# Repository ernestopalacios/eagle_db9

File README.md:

# eagle_db9

ESPAÑOL:    

Esta librería esta destinada al diseño de tarjetas electronicas que permitan, adaptar los diferentes tipos de conectores seriales. Muchas veces necesitamos conectar dos elementos y es necesario adaptar el tipo de conector. 

Mediante el uso de estas tarjetas diseñadas en Eagle PCB se lo puede lograr de una manera mucho mas sencilla.

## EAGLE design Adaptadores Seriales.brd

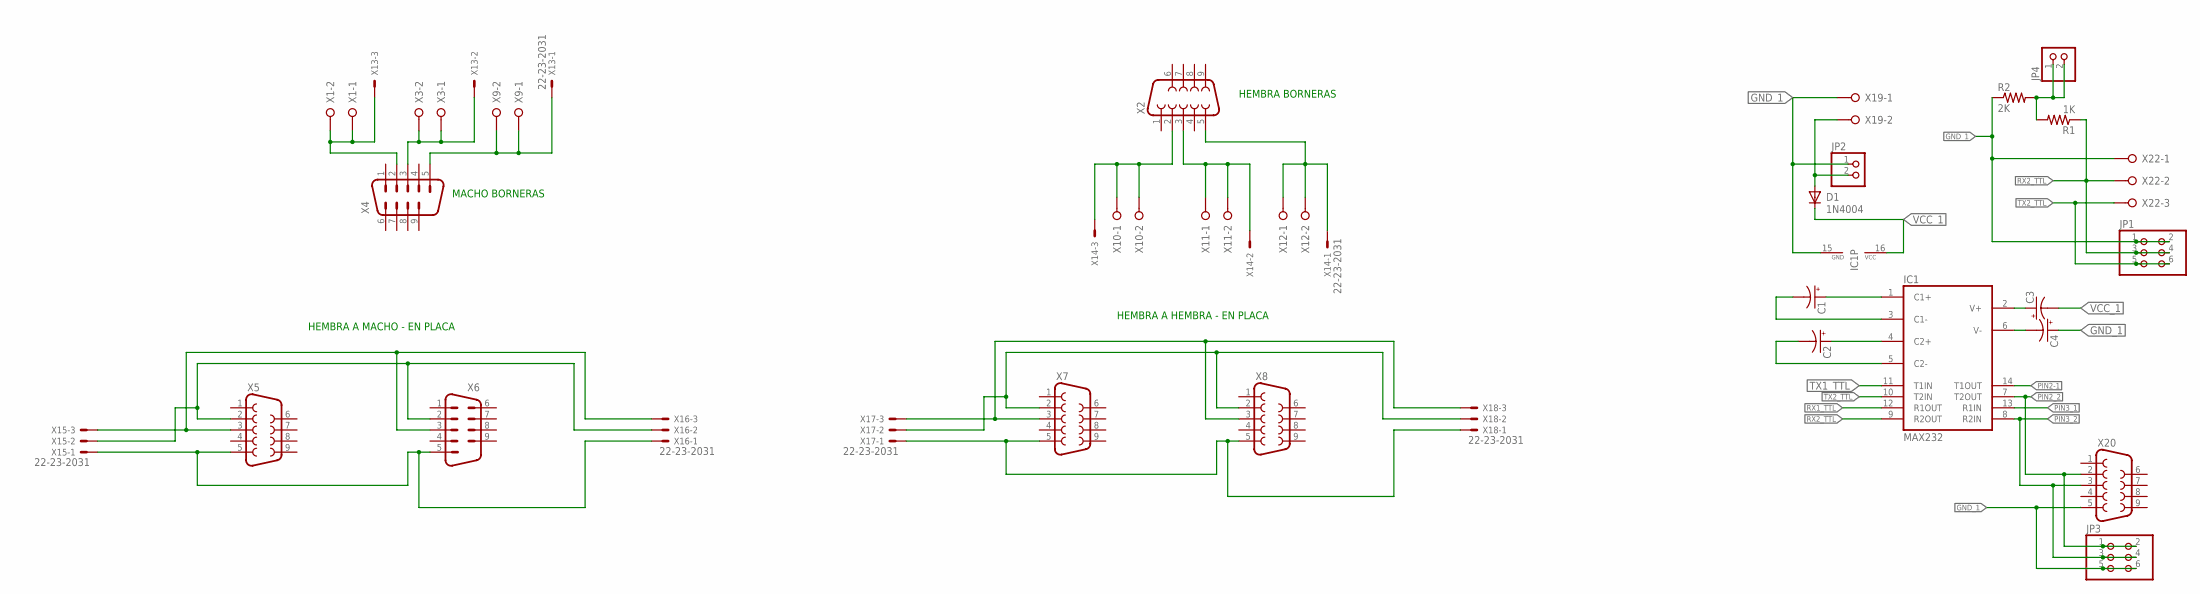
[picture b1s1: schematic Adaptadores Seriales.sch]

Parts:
C1, C2, C3, C4: 10UF-25V-20%(PTH)KIT; CPOL-RADIAL-10UF-25V-KIT
D1: 1N4004; DO41-10
IC1: MAX232; DIL16
JP1, JP3: PINHD-2X3; 2X03
JP2, JP4: PINHD-1X2; 1X02
R1: 1K; 0204V
R2: 2K; 0204V
X1, X3, X9, X10, X11, X12, X19: W237-02P; W237-132
X2: F09HP
X4: M09HP
X5, X7, X8, X20: F09D
X6: M09D
X13, X14, X15, X16, X17, X18: 22-23-2031
X22: W237-03P; W237-133

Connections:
GND_1: C4.1 (+), IC1.15 (GND), JP1.1, JP1.2, JP2.1, JP3.5, JP3.6, R2.1, X19.1, X20.5, X22.1
unnamed: C1.1 (+), IC1.1 (C1+)
unnamed: X5.2, X6.2, X15.2, X16.2
unnamed: X5.3, X6.3, X15.3, X16.3
unnamed: C1.2 (-), IC1.3 (C1-)
unnamed: X5.5, X6.5, X15.1, X16.1
unnamed: D1.A, JP2.2, X19.2
unnamed: C2.1 (+), IC1.4 (C2+)
unnamed: C2.2 (-), IC1.5 (C2-)
unnamed: C3.1 (+), IC1.2 (V+)
unnamed: C4.2 (-), IC1.6 (V-)
unnamed: X7.2, X8.2, X17.2, X18.2
unnamed: X7.3, X8.3, X17.3, X18.3
unnamed: JP4.1, JP4.2, R1.2, R2.2
unnamed: X7.5, X8.5, X17.1, X18.1
unnamed: X1.1, X1.2, X4.2, X13.3
unnamed: X3.1, X3.2, X4.3, X13.2
unnamed: X4.5, X9.1, X9.2, X13.1
unnamed: X2.2, X10.1, X10.2, X14.3
unnamed: X2.3, X11.1, X11.2, X14.2
unnamed: X2.5, X12.1, X12.2, X14.1
PIN2-1: IC1.14 (T1OUT)
PIN2_2: IC1.7 (T2OUT), JP3.1, JP3.2, X20.2
PIN3_1: IC1.13 (R1IN)
PIN3_2: IC1.8 (R2IN), JP3.3, JP3.4, X20.3
RX1_TTL: IC1.12 (R1OUT)
RX2_TTL: IC1.9 (R2OUT), JP1.3, JP1.4, R1.1, X22.2
TX1_TTL: IC1.11 (T1IN)
TX2_TTL: IC1.10 (T2IN), JP1.5, JP1.6, X22.3
VCC_1: C3.2 (-), D1.C, IC1.16 (VCC)

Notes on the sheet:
HEMBRA A MACHO - EN PLACA
HEMBRA A HEMBRA - EN PLACA
MACHO BORNERAS
HEMBRA BORNERAS

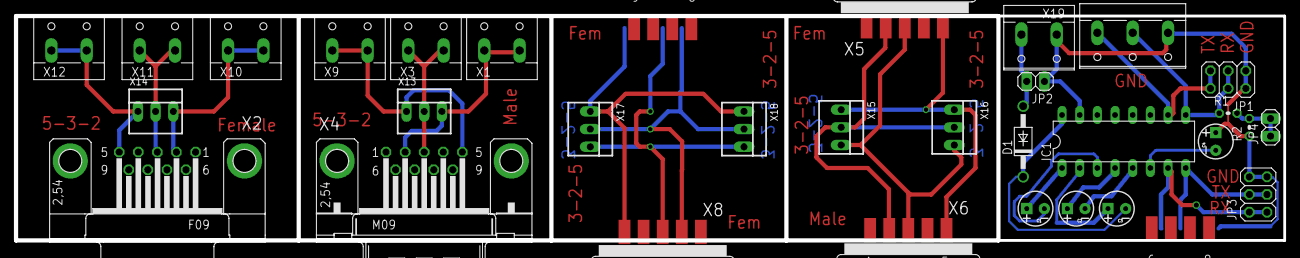
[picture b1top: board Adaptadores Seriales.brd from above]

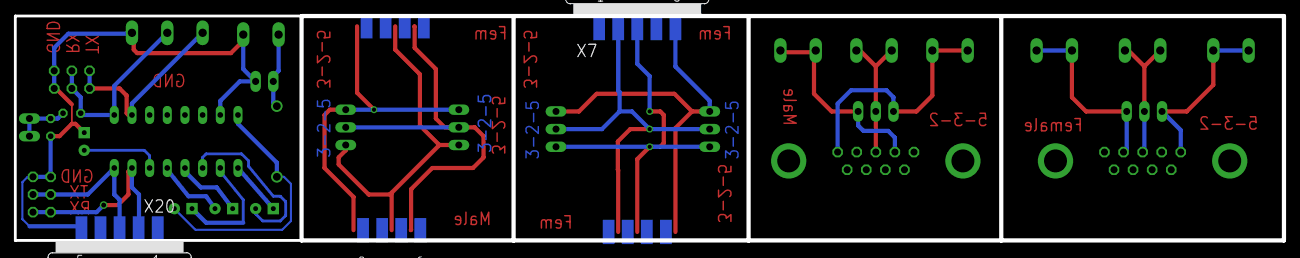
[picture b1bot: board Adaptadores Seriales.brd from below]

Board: 2 copper layers, 182.3 x 32.3 mm, 33 parts (2 on the bottom side), 26 nets.

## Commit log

2014-09-08 version 0.1.0 - Primera version - EAGLE 6.10
2015-01-07 Añadido Conversor MAX-232, con pine de 3v3 para Raspberry
2015-01-24 Create README.md
    Added first documentation

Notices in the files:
parts and their libraries:
SparkFun-Capacitors: Licensing: Creative Commons ShareAlike 4.0 International - https://creativecommons.org/licenses/by-sa/4.0
